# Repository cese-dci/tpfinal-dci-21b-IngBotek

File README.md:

## Trabajo práctico final de la asignatura DCI ##
Este repositorio contiene el trabajo práctico final para la asignatura de Diseño de Circuitos Impresos de la carrera de posgrado de FIUBA.

* Autor: Christian Canaan Castro Botek
* Título corto del trabajo:  Replica ublox NEO-6M GPS module
* Descripción: Módulo receptor que puede ser utilizado en cualquier aplicación que requiera geolocalización, cuenta con una antena de gran potencia, posee una memoria EEPROM para guardar datos y una batería para respaldar la configuración del módulo. Es compatible con Arduino, PIC, AVR, Raspberry y otros microcontroladores.

## Licencia de este trabajo ##
XXXMENCIONAR ACÁ LA LICENCIAXXX (Editar este párrafo) 
Y además colcar el archivo de texto de la misma en el directorio raíz.
Para este TP se pide que la licencia sea de hardware abierto.
Ver la sección "What license should I use?": https://www.oshwa.org/faq/

## Estructura del TP FINAL ##

Se propone y se pide utilizar la siguiente estructura.

* doc: Toda la información sobre el circuito, principalmente de autoría o procesamiento propio. Por ejemplo:
  * Notas de ingeniería propias.
  * Notas de aplicación propias.
  * Estudios previos, estado del arte, resumen de las investigaciones.
  * Notas con cálculos.
  * Dibujos adicionales.
  * Fotos de los prototipos.
  * Presupuestos, cotizaciones.
* info: Toda la iformación recolectada, principalmente de terceros, como por ejemplo:
  * Hojas de datos.
  * Notas de aplicación.
  * Info de productos comerciales.
  * Info en internet.
* pcb: Archivos de diseño esquemático y pcb.

Dependiendo la magnitud del proyecto, tendremos más o menos información en estos directorios. 
Revisar los README.md en cada directorio para conocer las pautas de cada uno para este TP.

NOTA: El alumno puede y debe borrar de este archivo todo lo que considere necesario, por ejemplo las aclaraciones del docente y esta misma nota.

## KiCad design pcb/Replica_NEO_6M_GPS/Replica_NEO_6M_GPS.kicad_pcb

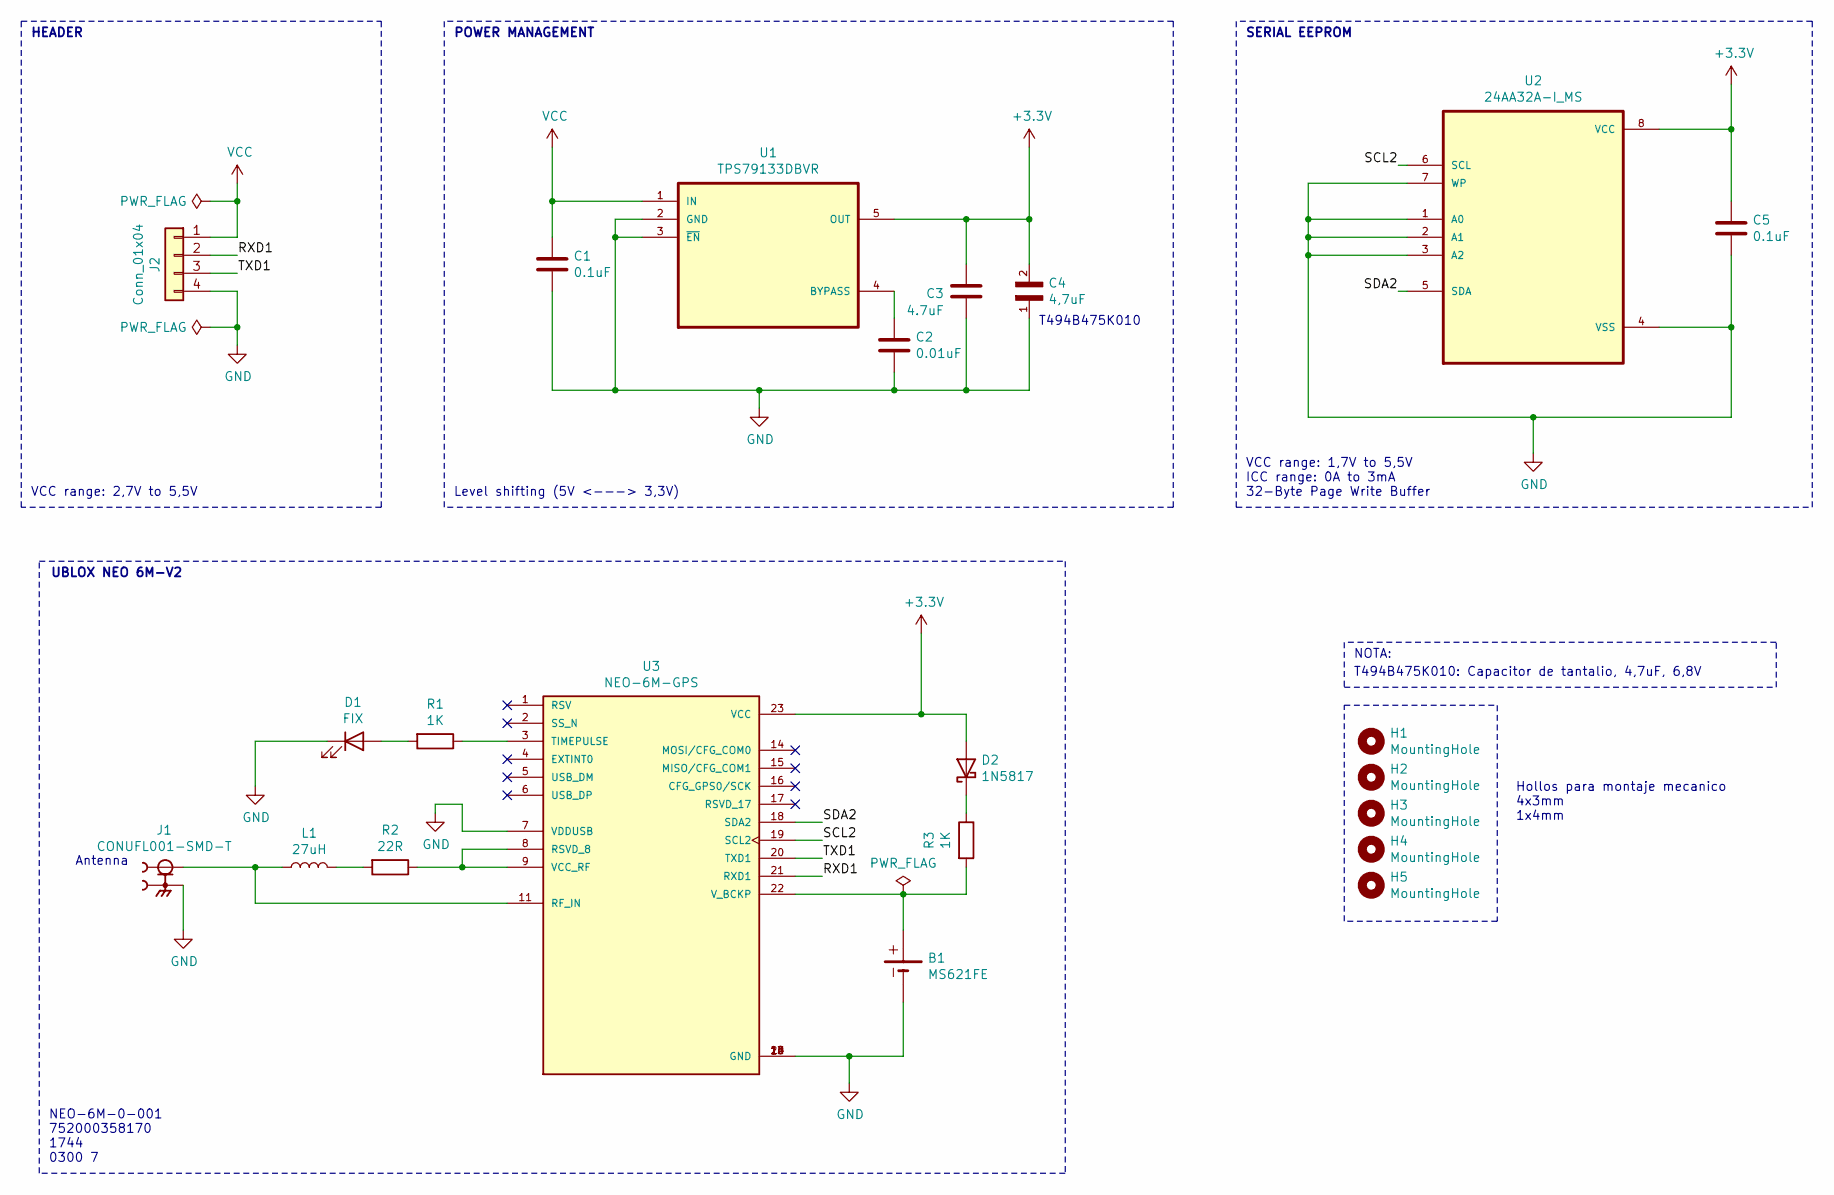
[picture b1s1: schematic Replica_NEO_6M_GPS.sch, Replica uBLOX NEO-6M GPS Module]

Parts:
B1: MS621FE
C1, C5: 0.1uF; C_0805_2012Metric_Pad1.18x1.45mm_HandSolder
C2: 0.01uF; C_0805_2012Metric_Pad1.18x1.45mm_HandSolder
C3: 4.7uF; C_0805_2012Metric_Pad1.18x1.45mm_HandSolder
C4: 4,7uF; CAPC2012X140N
D1: FIX; LED_0805_2012Metric_Pad1.15x1.40mm_HandSolder
D2: 1N5817; D_0805_2012Metric_Pad1.15x1.40mm_HandSolder
H1, H2, H3, H4: MountingHole; MountingHole_3mm
H5: MountingHole; MountingHole_4mm
J1: CONUFL001-SMD-T; LINX_CONUFL001-SMD-T; PARTREV B
J2: Conn_01x04; PinHeader_1x04_P2.54mm_Horizontal
L1: 27uH; L_0805_2012Metric_Pad1.15x1.40mm_HandSolder
R1, R3: 1K; R_0805_2012Metric_Pad1.20x1.40mm_HandSolder
R2: 22R; R_0805_2012Metric_Pad1.20x1.40mm_HandSolder
U1: TPS79133DBVR; SOT95P280X145-5N
U2: 24AA32A-I_MS; SOP65P490X110-8N
U3: NEO-6M-GPS; XCVR_NEO-6M-GPS; PARTREV R15

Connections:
+3V3: C3.1, C4.2, C5.1, D2.2 (A), U1.5 (OUT), U2.8 (VCC), U3.23 (VCC)
/RXD1: J2.2, U3.21 (RXD1)
/SCL2: U2.6 (SCL), U3.19 (SCL2)
/SDA2: U2.5 (SDA), U3.18 (SDA2)
/TXD1: J2.3, U3.20 (TXD1)
GND: B1.-, C1.2, C2.2, C3.2, C4.1, C5.2, D1.1 (K), J1.2, J1.3, J2.4, U1.2 (GND), U1.3 (~EN), U2.1 (A0), U2.2 (A1), U2.3 (A2), U2.4 (VSS), U2.7 (WP), U3.7 (VDDUSB), U3.10 (GND), U3.12 (GND), U3.13 (GND), U3.24 (GND)
unnamed: B1.+, R3.2, U3.22 (V_BCKP)
unnamed: C2.1, U1.4 (BYPASS)
unnamed: D1.2 (A), R1.2
unnamed: D2.1 (K), R3.1
unnamed: J1.1, L1.1, U3.11 (RF_IN)
unnamed: L1.2, R2.2
unnamed: R1.1, U3.3 (TIMEPULSE)
unnamed: R2.1, U3.8 (RSVD_8), U3.9 (VCC_RF)
VCC: C1.1, J2.1, U1.1 (IN)

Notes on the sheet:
Hollos para montaje mecanico 4x3mm 1x4mm
Antenna
HEADER
VCC range: 2,7V to 5,5V
POWER MANAGEMENT
Level shifting (5V <---> 3,3V)
SERIAL EEPROM
UBLOX NEO 6M-V2
T494B475K010
VCC range: 1,7V to 5,5V ICC range: 0A to 3mA 32-Byte Page Write Buffer
NEO-6M-0-001 752000358170 1744 0300 7
T494B475K010: Capacitor de tantalio, 4,7uF, 6,8V
NOTA:

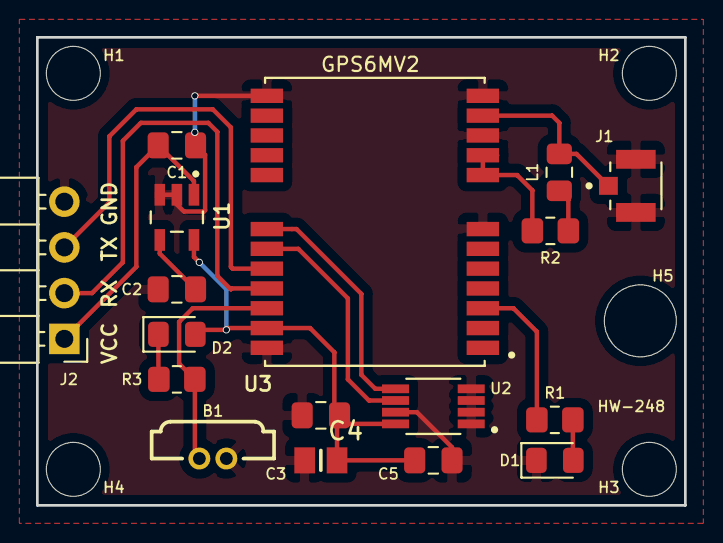
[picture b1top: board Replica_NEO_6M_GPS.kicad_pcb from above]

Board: 2 copper layers, 36.0 x 26.0 mm, 22 parts (0 on the bottom side), 15 nets.

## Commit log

2021-07-12 Se cargan archivos de propuesta e info
2021-07-12 se agrega esquematico y librerias
2021-07-12 se hicieron correcciones
2021-08-02 Se agregaron footprints y se hicieron correcciones menores
2021-08-15 Se hicieron correcciones y se avanzo con el PCB
2021-08-15 Se hicieron cambiaron los footprints de los LEDS D1,D2
2021-08-15 Se ajusto el margen para el componente U2
2021-08-15 Se hicieron correcciones menores
2021-08-17 Se acomodaron archivos y se hicieron retoques
2021-08-17 se retoco el esquematico
2021-08-19 Se acomodaron directorios y se hicieron correcciones
2021-08-23 Se hiceron correcciones 23/08/2021

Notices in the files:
pcb/Replica_NEO_6M_GPS/Replica_NEO_6M_GPS.kicad_pcb:
Copyright © 2011, u-blox AG
